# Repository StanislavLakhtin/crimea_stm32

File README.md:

# crimea_opendac
16 bit usb headphone amplifier on PCM1794A+PGA4311+OPA4134 managed by stm32f103

## Note

It completely doesn't work now.

## CLion Build Env

-DCMAKE_TOOLCHAIN_FILE=libopencm3.cmake

## About

This is complicated "hello world" project for standalone usb sound card and headphone amplifier based on Texas Instruments PCM2707 and STM Cortex-M3 STMF1.

Создаю этот проект для удовольствия. Если исходные коды проекта, схемы или другие материалы проекта будут полезны, буду очень рад.

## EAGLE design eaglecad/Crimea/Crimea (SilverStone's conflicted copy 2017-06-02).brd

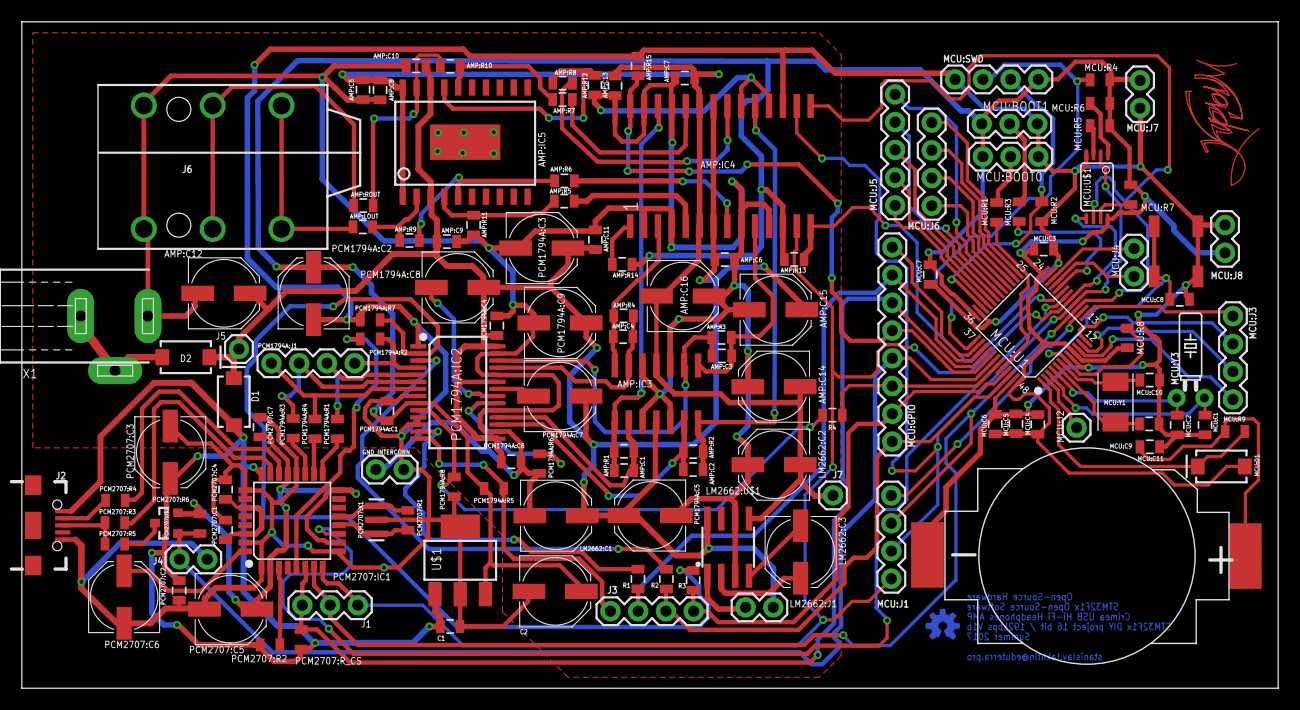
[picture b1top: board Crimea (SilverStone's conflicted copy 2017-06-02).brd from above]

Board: 2 copper layers, 115.0 x 61.0 mm, 136 parts (1 on the bottom side), 104 nets.

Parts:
AMP:C1, AMP:C2, AMP:C3, AMP:C4: 2.7nF; 0805
AMP:C5, AMP:C6, AMP:C7, AMP:C9, AMP:C11, AMP:C13: 0.1uF; 0805
AMP:C8, AMP:C10: 10uF; 0805
AMP:C12, AMP:C14: 10uF; PANASONIC_D
AMP:C15, AMP:C16: 100uF; PANASONIC_D
AMP:IC3: OPA4134D; SO14
AMP:IC4: PGA4311; SOP28
AMP:IC5: TPA6120A2; SOIC20S
AMP:LOUT: 37,8; 0805
AMP:R1, AMP:R2, AMP:R3, AMP:R4, AMP:R5, AMP:R6, AMP:R7, AMP:R8, AMP:R9, AMP:R10, AMP:R11, AMP:R12: 1K; 0805
AMP:R13, AMP:R14, AMP:R15: 100K; 0805
AMP:ROUT: 37,8; 0805
C1: 1.5uF; 0805
C2: 220uF; PANASONIC_D
D1: 0.5A/5V; SMA-DIODE
D2: 1.5A/5V; SMA-DIODE
GND_INTERCONN: GNDCONNECTOR; 1X02
J1: SPI; 1X03
J2: USB_MICRO; USB-AB-MICRO-SMD
J3: SWITCHERS; 1X04
J4: PULLUP; 1X02
J5: V+; 1X01
J6: HEADPHONES; AUDIO_JACK_0.25"_TRS_PTH_RA
J7: 1X01
LM2662:C1: 150nF; PANASONIC_D
LM2662:C2, LM2662:C3: 47uF; PANASONIC_D
LM2662:J1: 20/150Khz; 1X02
LM2662:U$1: LM2662; SOIC-8
MCU:BOOT0, MCU:BOOT1: 1X03
MCU:C1, MCU:C2, MCU:C8, MCU:C9, MCU:C10: 22pF; 0805
MCU:C3, MCU:C4, MCU:C5, MCU:C6, MCU:C7: 1uF; 0805
MCU:C11: 100nF; 0805
MCU:D1: 1A/5V/500mV; SMA-DIODE
MCU:GPIO: GPIO; 1X08
MCU:J1: SPI1; 1X04
MCU:J2: 1X01
MCU:J3: USART2; 1X04
MCU:J4: I2C_2; 1X02
MCU:J5: USART1; 1X05
MCU:J6: SPI2; 1X04
MCU:J7, MCU:J8: POWER; 1X02
MCU:R1, MCU:R2, MCU:R5, MCU:R6, MCU:R7, MCU:R8: 100K; 0805
MCU:R3, MCU:R4: 10K; 0805
MCU:R9: 100; 0805
MCU:SWD: DEBUG; 1X04
MCU:U1: STM32F103CBT6-LQFP48; LQFP48-0.5-7X7MM
MCU:U$1: M95320-D; TSSOP8
MCU:U$2: PUSHBUTTON; PUSHBUTTON_4X4
MCU:U$3: 20MM_BATTERY_3V
MCU:Y1: 16 Mhz; CRYSTAL-TXC-7A
MCU:Y3: 32.768kHz; CRYSTAL-PTH-2X6-CYL-KIT
PCM1794A:C1, PCM1794A:C4, PCM1794A:C6: 0.1uF; 0805
PCM1794A:C2, PCM1794A:C3, PCM1794A:C5, PCM1794A:C9, PCM2707:C5, PCM2707:C6: 10uF; PANASONIC_D
PCM1794A:C7, PCM1794A:C8: 47uF; PANASONIC_D
PCM1794A:IC2: PCM1794A; SSOP28-0.65-10.2X5.2MM
PCM1794A:J1: I2S; 1X04
PCM1794A:R1, PCM1794A:R5: 27; 0805
PCM1794A:R2, PCM1794A:R3, PCM1794A:R4: 10; 0805
PCM1794A:R6: 10K; 0805
PCM1794A:R7, PCM1794A:R8: 100K; 0805
PCM2707:C1, PCM2707:C2, PCM2707:C4, PCM2707:C7: 1uF; 0805
PCM2707:C3: 0.1uF; PANASONIC_D
PCM2707:IC1: PCM2707; TQFP32-0.8-7X7MM
PCM2707:R1: 1M; 0805
PCM2707:R2: 400k; 0805
PCM2707:R3, PCM2707:R4: 22; 0805
PCM2707:R5: 1.5K; 0805
PCM2707:R6: 400K; 0805
PCM2707:R_CS: 100k; 0805
PCM2707:U$2: IRLML2246TRPBF; SOT23-3
PCM2707:X1: 12MHz CSTCE12MOG52-R0; RESONATOR-SMD-3.2X1.3
R1, R2, R3, R4: 20; 0805
U$1: LM3940IMP-3.3/NOPB; SOT223
U$2: OSHW-LOGO-S_COPPER
U$3: CRIMEA_TOP
X1: EXT_+5V; 733980-62

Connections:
!AMP_MUTE!: AMP:IC4.1, AMP:R14.2
!PCM2702_CS!: J1.3, MCU:GPIO.6, MCU:U1.40, PCM2707:IC1.6, PCM2707:R_CS.1
!PGA4311_CS!: AMP:IC4.14, AMP:R13.2, MCU:U1.19
!RST!: J3.1, PCM1794A:IC2.14, PCM1794A:R5.1
!SSPND!: MCU:U1.18, PCM2707:IC1.11
+3.3V: AMP:IC4.12, AMP:R13.1, AMP:R14.1, C2.+, MCU:BOOT0.3, MCU:BOOT1.3, MCU:C3.2, MCU:C4.2, MCU:C5.2, MCU:C6.2, MCU:C7.2, MCU:D1.A, MCU:J7.1, MCU:J8.1, MCU:R4.2, MCU:R5.2, MCU:R6.2, MCU:R7.2, MCU:R8.2, MCU:SWD.1, MCU:U1.9, MCU:U1.24, MCU:U1.36, MCU:U1.48, MCU:U$1.8, PCM1794A:C1.2, PCM1794A:C2.+, PCM1794A:IC2.9, PCM1794A:R5.2, U$1.3
AMP:AMP_A: AMP:C1.1, AMP:IC3.1, AMP:IC4.26, AMP:R1.1
AMP:AMP_B: AMP:C2.1, AMP:IC3.7, AMP:IC4.19, AMP:R2.1
AMP:AMP_C: AMP:C3.1, AMP:IC3.8, AMP:IC4.10, AMP:R3.1
AMP:AMP_D: AMP:C4.1, AMP:IC3.14, AMP:IC4.3, AMP:R4.1
AMP:N$2: AMP:IC5.5, AMP:R6.1, AMP:R9.2
AMP:N$3: AMP:IC5.4, AMP:R5.1, AMP:R11.1
AMP:N$5: AMP:IC5.16, AMP:R7.1, AMP:R10.2
AMP:N$6: AMP:IC5.17, AMP:R8.1, AMP:R12.1
AMP:N$8: AMP:IC5.2, AMP:LOUT.2, AMP:R9.1
AMP:N$9: AMP:IC5.19, AMP:R10.1, AMP:ROUT.2
AMP:VOL_A: AMP:IC4.24, AMP:R7.2
AMP:VOL_B: AMP:IC4.21, AMP:R8.2
AMP:VOL_C: AMP:IC4.8, AMP:R6.2
AMP:VOL_D: AMP:IC4.5, AMP:R5.2
CHSL: PCM1794A:IC2.2, PCM1794A:R7.2, R3.2
DEM: PCM1794A:IC2.3, R2.2
DGND: AMP:IC4.17, AMP:R15.1, C1.2, C2.-, GND_INTERCONN.2, J2.GND1, J4.2, MCU:BOOT0.1, MCU:BOOT1.1, MCU:C1.1, MCU:C2.1, MCU:C3.1, MCU:C4.1, MCU:C5.1, MCU:C6.1, MCU:C7.1, MCU:C8.1, MCU:C9.1, MCU:C10.1, MCU:C11.1, MCU:J7.2, MCU:J8.2, MCU:R3.1, MCU:SWD.4, MCU:U1.8, MCU:U1.23, MCU:U1.35, MCU:U1.47, MCU:U$1.4, MCU:U$2.P$3, MCU:U$2.P$4, MCU:U$3.MINUS, PCM1794A:C1.1, PCM1794A:C2.-, PCM1794A:IC2.1, PCM1794A:IC2.8, PCM1794A:IC2.11, PCM1794A:IC2.12, PCM1794A:R7.1, PCM1794A:R8.1, PCM2707:C1.2, PCM2707:C2.1, PCM2707:C3.-, PCM2707:C4.1, PCM2707:C5.-, PCM2707:C6.-, PCM2707:C7.1, PCM2707:IC1.1, PCM2707:IC1.9, PCM2707:IC1.20, PCM2707:IC1.25, PCM2707:IC1.26, PCM2707:IC1.31, PCM2707:X1.2, U$1.2, U$1.4
EXT+5V: D2.A, X1.2, X1.3
GND: AMP:C5.2, AMP:C6.2, AMP:C7.2, AMP:C8.2, AMP:C9.2, AMP:C10.2, AMP:C11.1, AMP:C12.-, AMP:C13.2, AMP:C14.+, AMP:C15.-, AMP:C16.+, AMP:IC3.3, AMP:IC3.5, AMP:IC3.10, AMP:IC3.12, AMP:IC4.2, AMP:IC4.4, AMP:IC4.9, AMP:IC4.11, AMP:IC4.18, AMP:IC4.20, AMP:IC4.25, AMP:IC4.27, AMP:R11.2, AMP:R12.2, GND_INTERCONN.1, J6.SLEEVE, J6.SLEEVE-NORM, LM2662:C1.-, LM2662:C2.+, LM2662:U$1.3, LM2662:U$1.6, PCM1794A:C3.-, PCM1794A:C4.2, PCM1794A:C5.-, PCM1794A:C6.1, PCM1794A:C9.-, PCM1794A:IC2.16, PCM1794A:IC2.19, PCM1794A:IC2.24, PCM1794A:IC2.27, PCM1794A:R6.2, X1.1
LM2662:FC: LM2662:J1.1, LM2662:U$1.1
LM2662:N$1: LM2662:C3.+, LM2662:U$1.2
LM2662:N$2: LM2662:C3.-, LM2662:U$1.4
MCU:!EEPROM_CS!: MCU:R6.1, MCU:U$1.1
MCU:!EEPROM_HOLD!: MCU:R7.1, MCU:U$1.7
MCU:!RST!: MCU:C8.2, MCU:R8.1, MCU:U1.7, MCU:U$2.P$1, MCU:U$2.P$2
MCU:!W!: MCU:R5.1, MCU:U$1.3
MCU:BOOT0: MCU:R1.2, MCU:U1.44
MCU:I2C2_SCL: MCU:J4.2, MCU:U1.21
MCU:I2C2_SDA: MCU:J4.1, MCU:U1.22
MCU:N$1: MCU:D1.C, MCU:R9.2, MCU:U1.1
MCU:N$3: MCU:C11.2, MCU:R9.1, MCU:U$3.PLUS
MCU:N$7: MCU:BOOT0.2, MCU:R1.1
MCU:N$10: MCU:BOOT1.2, MCU:R2.1
MCU:OSC32_IN: MCU:C1.2, MCU:U1.3, MCU:Y3.2
MCU:OSC32_OUT: MCU:C2.2, MCU:U1.4, MCU:Y3.1
MCU:OSC_IN: MCU:C9.2, MCU:U1.5, MCU:Y1.P$2
MCU:OSC_OUT: MCU:C10.2, MCU:U1.6, MCU:Y1.P$1
MCU:PA8: MCU:J5.5, MCU:U1.29
MCU:PA9: MCU:J5.4, MCU:U1.30
MCU:PA10: MCU:J5.3, MCU:U1.31
MCU:PA11: MCU:J5.2, MCU:U1.32
MCU:PA12: MCU:J5.1, MCU:U1.33
MCU:PA15: MCU:GPIO.8, MCU:U1.38
MCU:PB2: MCU:R2.2, MCU:U1.20
MCU:PB15: MCU:J6.1, MCU:U1.28
MCU:PC13: MCU:J2.1, MCU:U1.2
MCU:SPI1_NSS: MCU:J1.4, MCU:U1.14
MCU:SPI2_MISO: MCU:J6.2, MCU:U1.27
MCU:SPI2_NSS: MCU:J6.4, MCU:U1.25
MCU:SPI2_SCK: MCU:J6.3, MCU:U1.26
MCU:SWDCLK: MCU:R4.1, MCU:SWD.3, MCU:U1.37
MCU:SWDIO: MCU:R3.2, MCU:SWD.2, MCU:U1.34
MCU:USART2_CTS: MCU:J3.4, MCU:U1.10
MCU:USART2_RTS: MCU:J3.3, MCU:U1.11
MCU:USART2_RX: MCU:J3.1, MCU:U1.13
MCU:USART2_TX: MCU:J3.2, MCU:U1.12
MUTE: MCU:GPIO.3, MCU:U1.43, R4.1
unnamed: J2.D-1, PCM2707:R4.2
unnamed: J2.D+1, PCM2707:R3.2, PCM2707:R5.2
unnamed: AMP:C3.2, AMP:IC3.9, AMP:R3.2, PCM1794A:IC2.26
unnamed: AMP:LOUT.1, J6.TIP, J6.TIP-NORM
unnamed: PCM1794A:R4.1, PCM2707:IC1.18
unnamed: PCM1794A:R2.1, PCM2707:IC1.5
unnamed: PCM1794A:R3.1, PCM2707:IC1.19
unnamed: PCM1794A:R1.1, PCM2707:IC1.17
unnamed: AMP:ROUT.1, J6.RING, J6.RING-NORM
unnamed: AMP:C4.2, AMP:IC3.13, AMP:R4.2, PCM1794A:IC2.25
unnamed: PCM1794A:IC2.10, PCM1794A:R8.2, R4.2
unnamed: AMP:C1.2, AMP:IC3.2, AMP:R1.2, PCM1794A:IC2.18
unnamed: AMP:C2.2, AMP:IC3.6, AMP:R2.2, PCM1794A:IC2.17
PB3: J3.2, MCU:GPIO.7, MCU:U1.39, R1.1
PB8: J3.4, MCU:GPIO.2, MCU:U1.45, R3.1
PB9: J3.3, MCU:GPIO.1, MCU:U1.46, R2.1
PCM1794A:BCK_INT: PCM1794A:IC2.6, PCM1794A:J1.2, PCM1794A:R3.2
PCM1794A:DATA_INT: PCM1794A:IC2.5, PCM1794A:J1.3, PCM1794A:R1.2
PCM1794A:LRCK_INT: PCM1794A:IC2.4, PCM1794A:J1.4, PCM1794A:R2.2
PCM1794A:N$4: PCM1794A:IC2.20, PCM1794A:R6.1
PCM1794A:N$9: PCM1794A:C7.-, PCM1794A:IC2.22
PCM1794A:N$10: PCM1794A:C8.-, PCM1794A:IC2.21
PCM1794A:SCK_INT: PCM1794A:IC2.7, PCM1794A:J1.1, PCM1794A:R4.2
PCM2707:INTRNL_D+: PCM2707:IC1.23, PCM2707:R3.1
PCM2707:INTRNL_D-: PCM2707:IC1.22, PCM2707:R4.1
PCM2707:INTRNL_HOST: PCM2707:IC1.3, PCM2707:R2.2
PCM2707:INT_3.3V: PCM2707:C5.+, PCM2707:C7.2, PCM2707:IC1.2, PCM2707:IC1.10, PCM2707:IC1.16, PCM2707:IC1.21, PCM2707:R6.1, PCM2707:U$2.2
PCM2707:N$2: PCM2707:C1.1, PCM2707:C4.2, PCM2707:IC1.27, PCM2707:IC1.30
PCM2707:N$9: PCM2707:R5.1, PCM2707:U$2.3
PCM2707:RESONATOR_XTI: PCM2707:IC1.12, PCM2707:R1.1, PCM2707:X1.1
PCM2707:RESONATOR_XTO: PCM2707:IC1.13, PCM2707:R1.2, PCM2707:X1.3
PCM2707:VCOM: PCM2707:C6.+, PCM2707:IC1.32
PULLUP_D+: J4.1, MCU:GPIO.4, MCU:U1.42, PCM2707:R6.2, PCM2707:U$2.1
SPI_MISO: AMP:IC4.16, MCU:J1.2, MCU:U1.16, MCU:U$1.2
SPI_MOSI: AMP:IC4.13, J1.1, MCU:J1.1, MCU:U1.17, MCU:U$1.5, PCM2707:IC1.8
SPI_SCK: AMP:IC4.15, J1.2, MCU:J1.3, MCU:U1.15, MCU:U$1.6, PCM2707:IC1.7
USB+5V: C1.1, D1.A, J2.VBUS1, PCM2707:C2.2, PCM2707:C3.+, PCM2707:IC1.24, PCM2707:R2.1, PCM2707:R_CS.2, U$1.1
V+: AMP:C6.1, AMP:C9.1, AMP:C10.1, AMP:C11.2, AMP:C12.+, AMP:C15.+, AMP:IC3.4, AMP:IC4.7, AMP:IC4.22, AMP:IC5.3, AMP:IC5.18, D1.C, D2.C, J5.1, LM2662:C1.+, LM2662:J1.2, LM2662:U$1.8, PCM1794A:C3.+, PCM1794A:C4.1, PCM1794A:C5.+, PCM1794A:C6.2, PCM1794A:C7.+, PCM1794A:C8.+, PCM1794A:C9.+, PCM1794A:IC2.15, PCM1794A:IC2.23, PCM1794A:IC2.28
V-: AMP:C5.1, AMP:C7.1, AMP:C8.1, AMP:C13.1, AMP:C14.-, AMP:C16.-, AMP:IC3.11, AMP:IC4.6, AMP:IC4.23, AMP:IC5.1, AMP:IC5.20, J7.1, LM2662:C2.-, LM2662:U$1.5
ZCEN: AMP:IC4.28, AMP:R15.2, MCU:GPIO.5, MCU:U1.41
ZERO: PCM1794A:IC2.13, R1.2

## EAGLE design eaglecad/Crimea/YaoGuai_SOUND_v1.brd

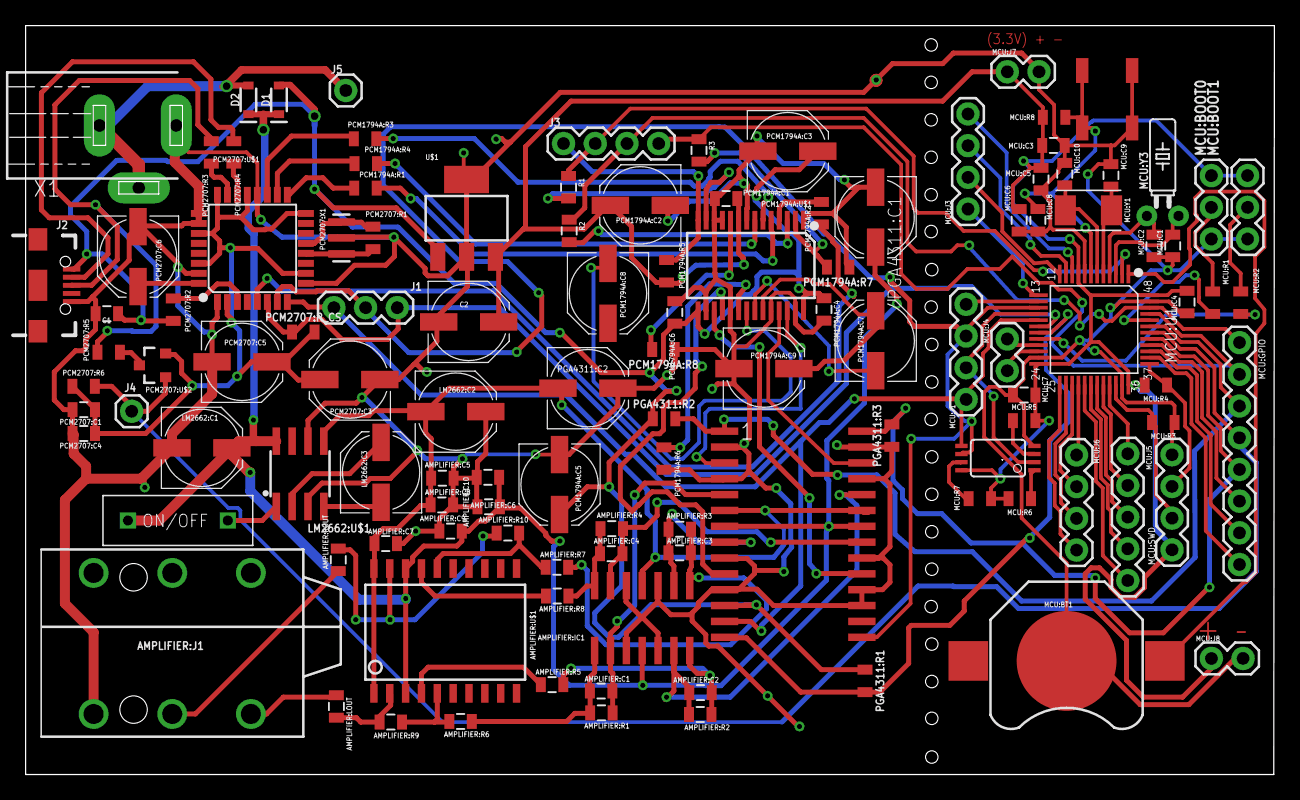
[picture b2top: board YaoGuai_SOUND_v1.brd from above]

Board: 2 copper layers, 100.0 x 60.0 mm, 118 parts (0 on the bottom side), 101 nets.

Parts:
AMPLIFIER:C1, AMPLIFIER:C2, AMPLIFIER:C3, AMPLIFIER:C4: 2.7nF; 0805
AMPLIFIER:C5, AMPLIFIER:C6, AMPLIFIER:C7, AMPLIFIER:C9: 0.1uF; 0805
AMPLIFIER:C8, AMPLIFIER:C10: 10uF; 0805
AMPLIFIER:IC1: OPA4134D; SO14
AMPLIFIER:J1: AUDIO_JACK_TRS_0.25"_PTH_RA; AUDIO_JACK_0.25"_TRS_PTH_RA
AMPLIFIER:LOUT: 50; 0805
AMPLIFIER:R1, AMPLIFIER:R2, AMPLIFIER:R3, AMPLIFIER:R4, AMPLIFIER:R5, AMPLIFIER:R6, AMPLIFIER:R7, AMPLIFIER:R8, AMPLIFIER:R9, AMPLIFIER:R10: 1K; 0805
AMPLIFIER:ROUT: 50; 0805
AMPLIFIER:U$1: TPA6120A2; SOIC20S
C1: 1.5uF; 0805
C2: 220uF; PANASONIC_D
D1, D2: 0.5A/40V/420mV; SOD-323
J1: 1X03
J2: USB-AB-MICRO-SMD
J3: 1X04
J4, J5: 1X01
LM2662:C1: 150nF; PANASONIC_D
LM2662:C2, LM2662:C3: 47uF; PANASONIC_D
LM2662:U$1: LM2662; SOIC-8
LM2662:U$2: RED_SWITCH_ON; RED_SWITCH
MCU:BOOT0, MCU:BOOT1: 1X03
MCU:BT1: BATTCON_12MM
MCU:C1, MCU:C2, MCU:C8, MCU:C9, MCU:C10: 22pF; 0805
MCU:C3, MCU:C4, MCU:C5, MCU:C6, MCU:C7: 1uF; 0805
MCU:GPIO: 1X08
MCU:J1: SPI1; 1X04
MCU:J3: USART2; 1X04
MCU:J4: I2C_2; 1X02
MCU:J5: USART1; 1X05
MCU:J6: SPI2; 1X04
MCU:J7, MCU:J8: POWER; 1X02
MCU:R1, MCU:R2, MCU:R5, MCU:R6, MCU:R7, MCU:R8: 100K; 0805
MCU:R3, MCU:R4: 10K; 0805
MCU:SWD: 1X04
MCU:U1: STM32F103CBT6-LQFP48; LQFP48-0.5-7X7MM
MCU:U$1: M95320-D; TSSOP8
MCU:U$2: PUSHBUTTON; PUSHBUTTON_4X4
MCU:Y1: CRYSTAL-TXC-7A
MCU:Y3: 32.768kHz; CRYSTAL-PTH-2X6-CYL-KIT
PCM1794A:C1, PCM1794A:C4, PCM1794A:C6: 0.1uF; 0805
PCM1794A:C2, PCM1794A:C3, PCM1794A:C5, PCM1794A:C9, PCM2707:C5, PCM2707:C6: 10uF; PANASONIC_D
PCM1794A:C7, PCM1794A:C8: 47uF; PANASONIC_D
PCM1794A:R1, PCM1794A:R2, PCM1794A:R3, PCM1794A:R4, PCM1794A:R5: 27; 0805
PCM1794A:R6: 10K; 0805
PCM1794A:R7, PCM1794A:R8: 100K; 0805
PCM1794A:U$1: PCM1794A; SSOP28-0.65-10.2X5.2MM
PCM2707:C1, PCM2707:C4: 1uF; 0805
PCM2707:C3: 0.1uF; PANASONIC_D
PCM2707:R1, PCM2707:R2, PCM2707:R6: 1M; 0805
PCM2707:R3, PCM2707:R4: 22; 0805
PCM2707:R5: 1.5K; 0805
PCM2707:R_CS: 100k; 0805
PCM2707:U$1: PCM2707; TQFP32-0.8-7X7MM
PCM2707:U$2: IRLML2246TRPBF; SOT23-3
PCM2707:X1: 12MHz; RESONATOR-SMD-3.2X1.3
PGA4311:C1, PGA4311:C2: PANASONIC_D
PGA4311:R1: 0805
PGA4311:R2, PGA4311:R3: 100K; 0805
PGA4311:U$1: PGA4311; SOP28
R1, R2, R3: 20; 0805
U$1: LM3940IMP-3.3/NOPB; SOT223
X1: 733980-62

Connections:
3.3V: C2.+, MCU:BOOT0.3, MCU:BOOT1.3, MCU:C3.2, MCU:C4.2, MCU:C5.2, MCU:C6.2, MCU:C7.2, MCU:J7.1, MCU:J8.1, MCU:R4.2, MCU:R5.2, MCU:R6.2, MCU:R7.2, MCU:R8.2, MCU:SWD.1, MCU:U1.9, MCU:U1.24, MCU:U1.36, MCU:U1.48, MCU:U$1.8, PCM1794A:C1.2, PCM1794A:C2.+, PCM1794A:R5.2, PCM1794A:U$1.9, U$1.3
!MUTE!: MCU:GPIO.3, MCU:U1.43, PGA4311:R2.2, PGA4311:U$1.1
!PCM2702_CS!: J1.3, MCU:U1.18, PCM2707:R_CS.1, PCM2707:U$1.6
!PGA4311_CS!: MCU:U1.19, PGA4311:R1.2, PGA4311:U$1.14
AMPLIFIER:N$1: AMPLIFIER:C1.1, AMPLIFIER:IC1.1, AMPLIFIER:R1.1, AMPLIFIER:R6.2
AMPLIFIER:N$2: AMPLIFIER:R6.1, AMPLIFIER:R9.2, AMPLIFIER:U$1.5
AMPLIFIER:N$3: AMPLIFIER:R5.1, AMPLIFIER:U$1.4
AMPLIFIER:N$4: AMPLIFIER:C2.1, AMPLIFIER:IC1.7, AMPLIFIER:R2.1, AMPLIFIER:R5.2
AMPLIFIER:N$5: AMPLIFIER:R7.1, AMPLIFIER:R10.2, AMPLIFIER:U$1.16
AMPLIFIER:N$6: AMPLIFIER:R8.1, AMPLIFIER:U$1.17
AMPLIFIER:N$7: AMPLIFIER:C3.1, AMPLIFIER:IC1.8, AMPLIFIER:R3.1, AMPLIFIER:R7.2
AMPLIFIER:N$8: AMPLIFIER:LOUT.2, AMPLIFIER:R9.1, AMPLIFIER:U$1.2
AMPLIFIER:N$9: AMPLIFIER:R10.1, AMPLIFIER:ROUT.2, AMPLIFIER:U$1.19
AMPLIFIER:N$10: AMPLIFIER:C4.1, AMPLIFIER:IC1.14, AMPLIFIER:R4.1, AMPLIFIER:R8.2
AMPLIFIER:N$11: AMPLIFIER:J1.RING, AMPLIFIER:ROUT.1
AMPLIFIER:N$12: AMPLIFIER:J1.TIP, AMPLIFIER:LOUT.1
CHSL: PCM1794A:R7.2, PCM1794A:U$1.2, R3.2
DEM: PCM1794A:U$1.3, R2.2
EXT+5V: D2.A, J5.1, X1.2, X1.3
GND: AMPLIFIER:C5.2, AMPLIFIER:C6.2, AMPLIFIER:C7.2, AMPLIFIER:C8.2, AMPLIFIER:C9.2, AMPLIFIER:C10.2, AMPLIFIER:IC1.3, AMPLIFIER:IC1.5, AMPLIFIER:IC1.10, AMPLIFIER:IC1.12, AMPLIFIER:J1.SLEEVE, C1.2, C2.-, J2.GND1, LM2662:C1.-, LM2662:C2.+, LM2662:U$1.3, LM2662:U$1.6, MCU:BOOT0.1, MCU:BOOT1.1, MCU:BT1.GND, MCU:C1.1, MCU:C2.1, MCU:C3.1, MCU:C4.1, MCU:C5.1, MCU:C6.1, MCU:C7.1, MCU:C8.1, MCU:C9.1, MCU:C10.1, MCU:J7.2, MCU:J8.2, MCU:R3.1, MCU:SWD.4, MCU:U1.8, MCU:U1.23, MCU:U1.35, MCU:U1.47, MCU:U$1.4, MCU:U$2.P$3, MCU:U$2.P$4, PCM1794A:C1.1, PCM1794A:C2.-, PCM1794A:C3.-, PCM1794A:C4.2, PCM1794A:C5.-, PCM1794A:C6.1, PCM1794A:C9.-, PCM1794A:R6.2, PCM1794A:R7.1, PCM1794A:R8.1, PCM1794A:U$1.1, PCM1794A:U$1.8, PCM1794A:U$1.11, PCM1794A:U$1.12, PCM1794A:U$1.16, PCM1794A:U$1.19, PCM1794A:U$1.24, PCM1794A:U$1.27, PCM2707:C1.2, PCM2707:C3.-, PCM2707:C4.1, PCM2707:C5.-, PCM2707:C6.-, PCM2707:U$1.1, PCM2707:U$1.9, PCM2707:U$1.20, PCM2707:U$1.25, PCM2707:U$1.26, PCM2707:U$1.31, PCM2707:X1.2, PGA4311:C1.-, PGA4311:C2.+, PGA4311:R3.1, PGA4311:U$1.2, PGA4311:U$1.4, PGA4311:U$1.9, PGA4311:U$1.11, PGA4311:U$1.17, PGA4311:U$1.18, PGA4311:U$1.20, PGA4311:U$1.25, PGA4311:U$1.27, U$1.2, U$1.4, X1.1
LM2662:FC: LM2662:U$1.1, LM2662:U$2.P$1
LM2662:N$1: LM2662:C3.+, LM2662:U$1.2
LM2662:N$2: LM2662:C3.-, LM2662:U$1.4
MCU:!EEPROM_CS!: MCU:R6.1, MCU:U$1.1
MCU:!EEPROM_HOLD!: MCU:R7.1, MCU:U$1.7
MCU:!RST!: MCU:C8.2, MCU:R8.1, MCU:U1.7, MCU:U$2.P$1, MCU:U$2.P$2
MCU:!W!: MCU:R5.1, MCU:U$1.3
MCU:I2C2_SCL: MCU:J4.2, MCU:U1.21
MCU:I2C2_SDA: MCU:J4.1, MCU:U1.22
MCU:N$1: MCU:BT1.PWR@1, MCU:U1.1
MCU:N$2: MCU:C10.2, MCU:U1.6, MCU:Y1.P$1
MCU:N$3: MCU:C9.2, MCU:U1.5, MCU:Y1.P$2
MCU:N$4: MCU:C2.2, MCU:U1.4, MCU:Y3.1
MCU:N$5: MCU:C1.2, MCU:U1.3, MCU:Y3.2
MCU:N$6: MCU:J5.3, MCU:U1.31
MCU:N$7: MCU:BOOT0.2, MCU:R1.1
MCU:N$8: MCU:R1.2, MCU:U1.44
MCU:N$9: MCU:J5.2, MCU:U1.32
MCU:N$10: MCU:BOOT1.2, MCU:R2.1
MCU:N$11: MCU:R2.2, MCU:U1.20
MCU:N$12: MCU:J5.1, MCU:U1.33
MCU:N$14: MCU:J5.4, MCU:U1.30
MCU:N$15: MCU:J5.5, MCU:U1.29
MCU:PA15: MCU:GPIO.8, MCU:U1.38
MCU:PB3: MCU:GPIO.7, MCU:U1.39
MCU:PB4: MCU:GPIO.6, MCU:U1.40
MCU:SPI1_MISO: MCU:J1.2, MCU:U1.16, MCU:U$1.2
MCU:SPI1_NSS: MCU:J1.4, MCU:U1.14
MCU:SPI2_MISO: MCU:J6.2, MCU:U1.27
MCU:SPI2_MOSI: MCU:J6.1, MCU:U1.28
MCU:SPI2_NSS: MCU:J6.4, MCU:U1.25
MCU:SPI2_SCK: MCU:J6.3, MCU:U1.26
MCU:SWDCLK: MCU:R4.1, MCU:SWD.3, MCU:U1.37
MCU:SWDIO: MCU:R3.2, MCU:SWD.2, MCU:U1.34
MCU:USART2_CTS: MCU:J3.4, MCU:U1.10
MCU:USART2_RTS: MCU:J3.3, MCU:U1.11
MCU:USART2_RX: MCU:J3.1, MCU:U1.13
MCU:USART2_TX: MCU:J3.2, MCU:U1.12
unnamed: J2.D-1, PCM2707:R4.2
unnamed: J2.D+1, PCM2707:R3.2, PCM2707:R5.2
unnamed: PCM1794A:U$1.26, PGA4311:U$1.3
unnamed: PCM1794A:U$1.25, PGA4311:U$1.26
unnamed: PCM1794A:R4.1, PCM2707:U$1.18
unnamed: PCM1794A:R2.1, PCM2707:U$1.5
unnamed: PCM1794A:R3.1, PCM2707:U$1.19
unnamed: PCM1794A:R1.1, PCM2707:U$1.17
unnamed: PCM1794A:U$1.18, PGA4311:U$1.10
unnamed: PCM1794A:U$1.17, PGA4311:U$1.19
unnamed: J3.2, MCU:U1.2, R1.1
unnamed: J3.3, MCU:GPIO.1, MCU:U1.46, R2.1
unnamed: J3.4, MCU:GPIO.2, MCU:U1.45, R3.1
unnamed: J3.1, PCM1794A:R5.1, PCM1794A:U$1.14
unnamed: AMPLIFIER:C3.2, AMPLIFIER:IC1.9, AMPLIFIER:R3.2, PGA4311:U$1.8
unnamed: AMPLIFIER:C4.2, AMPLIFIER:IC1.13, AMPLIFIER:R4.2, PGA4311:U$1.21
unnamed: AMPLIFIER:C2.2, AMPLIFIER:IC1.6, AMPLIFIER:R2.2, PGA4311:U$1.24
unnamed: AMPLIFIER:C1.2, AMPLIFIER:IC1.2, AMPLIFIER:R1.2, PGA4311:U$1.5
PCM1794A:MUTE: PCM1794A:R8.2, PCM1794A:U$1.10
PCM1794A:N$1: PCM1794A:R4.2, PCM1794A:U$1.7
PCM1794A:N$2: PCM1794A:R3.2, PCM1794A:U$1.6
PCM1794A:N$3: PCM1794A:R1.2, PCM1794A:U$1.5
PCM1794A:N$4: PCM1794A:R6.1, PCM1794A:U$1.20
PCM1794A:N$5: PCM1794A:R2.2, PCM1794A:U$1.4
PCM1794A:N$9: PCM1794A:C7.-, PCM1794A:U$1.22
PCM1794A:N$10: PCM1794A:C8.-, PCM1794A:U$1.21
PCM1794A:V+: PCM1794A:C7.+, PCM1794A:C8.+, PCM1794A:C9.+, PCM1794A:U$1.23
PCM2707:INTRNL_D+: PCM2707:R3.1, PCM2707:U$1.23
PCM2707:INTRNL_D-: PCM2707:R4.1, PCM2707:U$1.22
PCM2707:INTRNL_HOST: PCM2707:R2.2, PCM2707:U$1.3
PCM2707:N$9: PCM2707:R5.1, PCM2707:U$2.3
PCM2707:RESONATOR_XTI: PCM2707:R1.1, PCM2707:U$1.12, PCM2707:X1.1
PCM2707:RESONATOR_XTO: PCM2707:R1.2, PCM2707:U$1.13, PCM2707:X1.3
PCM2707:USB+5V: PCM2707:C1.1, PCM2707:C3.+, PCM2707:C4.2, PCM2707:C5.+, PCM2707:R6.1, PCM2707:R_CS.2, PCM2707:U$1.2, PCM2707:U$1.10, PCM2707:U$1.16, PCM2707:U$1.21, PCM2707:U$1.24, PCM2707:U$1.27, PCM2707:U$1.30, PCM2707:U$2.2
PCM2707:VCOM: PCM2707:C6.+, PCM2707:U$1.32
PULLUP_D+: J4.1, MCU:GPIO.4, MCU:U1.42, PCM2707:R6.2, PCM2707:U$2.1
SPI_MOSI: J1.1, MCU:J1.1, MCU:U1.17, MCU:U$1.5, PCM2707:U$1.8, PGA4311:U$1.13
SPI_SCK: J1.2, MCU:J1.3, MCU:U1.15, MCU:U$1.6, PCM2707:U$1.7, PGA4311:U$1.15
USB+5V: C1.1, D1.A, J2.VBUS1, PCM1794A:C3.+, PCM1794A:C4.1, PCM1794A:C5.+, PCM1794A:C6.2, PCM1794A:U$1.15, PCM1794A:U$1.28, PCM2707:R2.1, PGA4311:R1.1, PGA4311:R2.1, PGA4311:U$1.12, U$1.1
V+: AMPLIFIER:C6.1, AMPLIFIER:C9.1, AMPLIFIER:C10.1, AMPLIFIER:IC1.4, AMPLIFIER:U$1.3, AMPLIFIER:U$1.18, D1.C, D2.C, LM2662:C1.+, LM2662:U$1.8, LM2662:U$2.P$2, PGA4311:C1.+, PGA4311:U$1.7, PGA4311:U$1.22
V-: AMPLIFIER:C5.1, AMPLIFIER:C7.1, AMPLIFIER:C8.1, AMPLIFIER:IC1.11, AMPLIFIER:U$1.1, AMPLIFIER:U$1.20, LM2662:C2.-, LM2662:U$1.5, PGA4311:C2.-, PGA4311:U$1.6, PGA4311:U$1.23
ZCEN: MCU:GPIO.5, MCU:U1.41, PGA4311:R3.2, PGA4311:U$1.28
ZERO: PCM1794A:U$1.13, R1.2

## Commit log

2017-06-25 usb initial commit
2017-06-25 usb descriptor works
2017-06-26 still work on the USB descriptor. Added some needed structures.
2017-06-26 making descriptor step by step
2017-06-27 add a few new descriptor structs. Few things were added in config descriptor after.
2017-06-28 first run on stm32f107vc is wrong. It seems that linked script should be improved
2017-06-30 minor fixes
2017-07-02 minor improvments
2017-08-13 doesn't work
2018-05-09 EAGLE files copied into the project folder

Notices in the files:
parts and their libraries:
SparkFun-Passives: Licensing: Creative Commons ShareAlike 4.0 International - https://creativecommons.org/licenses/by-sa/4.0
